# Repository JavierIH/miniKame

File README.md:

> 📌 **A newer and more advanced version of this robot is available:** [Kame32](https://github.com/javierih/kame32)

# Kame (MiniKame)

[What components do I need for building this robot?](https://github.com/bqlabs/miniKame/wiki/BOM)

[Where can I find the assembly model?](https://github.com/bqlabs/miniKame/blob/develop/parts/freecad/miniKame.fcstd)

[How are servos connected to the NodeMCU V2 board?](https://github.com/JavierIH/miniKame/wiki/Map-between-servos-and-board-pins)

# License

Son of [Kame](https://github.com/bqlabs/kame)

# Remixes
[PoorKame](https://github.com/owenlab/PoorKame) by [owenlab](https://github.com/owenlab)

[FatKame](https://github.com/Blomdoft/fatKame) by [Blomdoft](https://github.com/Blomdoft)

# Other

Sponsored by BQ till march 2016

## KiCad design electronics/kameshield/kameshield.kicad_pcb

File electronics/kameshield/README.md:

# Attention:

This PCB is just a proof of concept of a shield for putting together the needed connectors for servos and battery on a NodeMCU V2. At this time, it has been fabricated an only one board (the one is actually being mounted on PoorKame) with a hobby-level milling machine, so I can't guarantee it to work or even if it is safe for being used with another specific hardware.

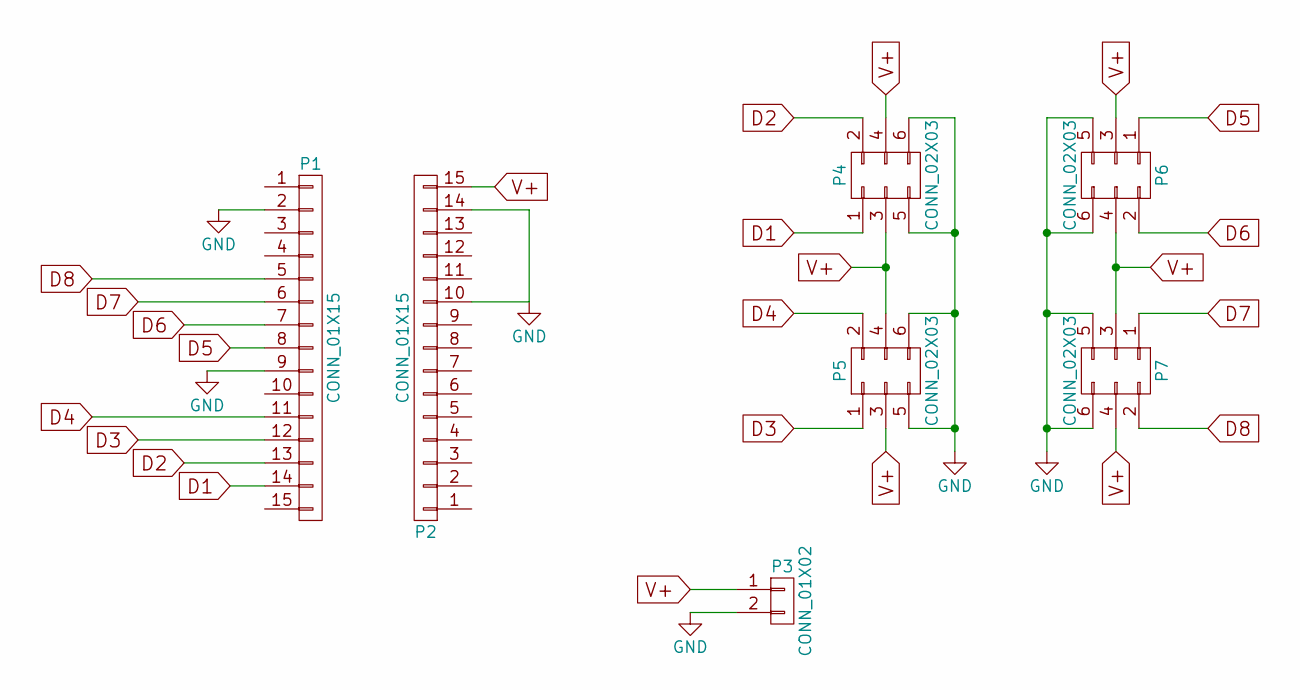
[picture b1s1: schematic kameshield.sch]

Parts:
P1, P2: CONN_01X15; Pin_Header_Straight_1x15
P3: CONN_01X02; Pin_Header_Straight_1x02
P4, P5, P6, P7: CONN_02X03; Pin_Header_Angled_2x03

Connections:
D1: P1.14, P4.1
D2: P1.13, P4.2
D3: P1.12, P5.1
D4: P1.11, P5.2
D5: P1.8, P6.1
D6: P1.7, P6.2
D7: P1.6, P7.1
D8: P1.5, P7.2
GND: P1.2, P1.9, P2.10, P2.14, P3.2, P4.5, P4.6, P5.5, P5.6, P6.5, P6.6, P7.5, P7.6
V+: P2.15, P3.1, P4.3, P4.4, P5.3, P5.4, P6.3, P6.4, P7.3, P7.4

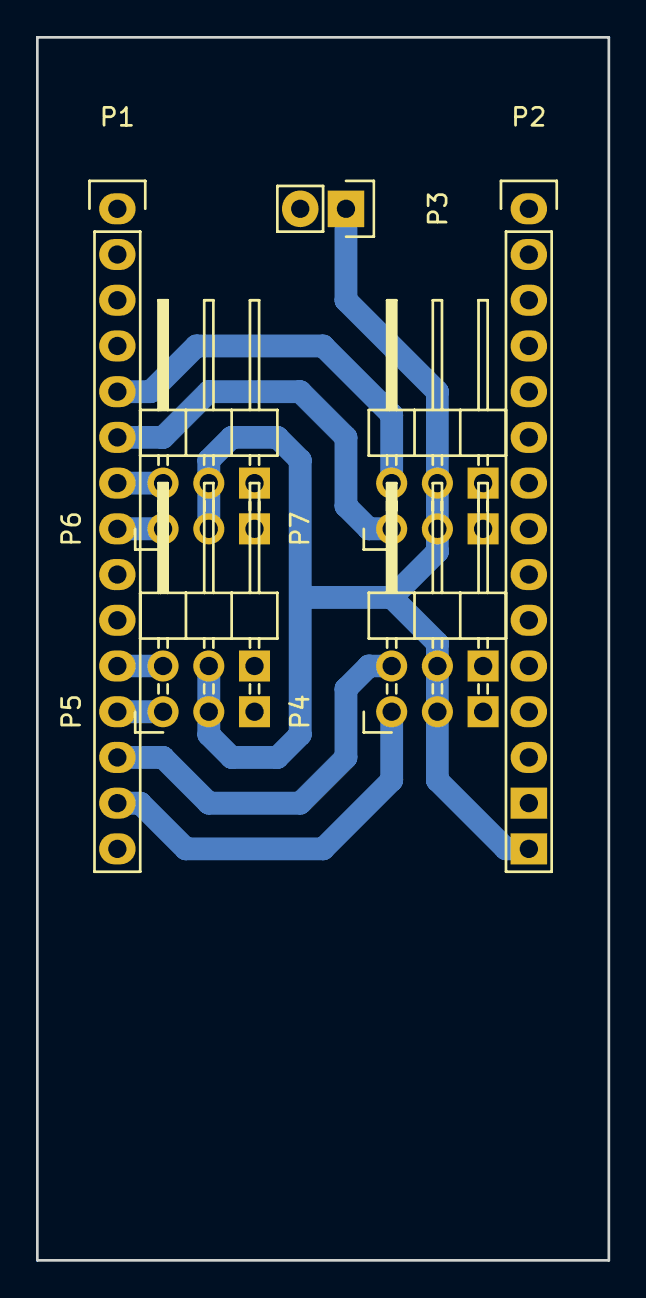
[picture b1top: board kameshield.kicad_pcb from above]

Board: 2 copper layers, 31.8 x 67.9 mm, 7 parts (0 on the bottom side), 10 nets.

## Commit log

2015-11-26 Add freecad project
2015-11-26 Add stl files
2015-11-30 updated body for nodemcu
2015-12-01 reinforced bearing cavitiy on legB
2015-12-01 Added bearings on 3d model
2015-12-02 added code structure
2015-12-02 moved ardusnake from src to lib
2015-12-14 updated 3d model
2015-12-14 new oscillator library
2015-12-15 added spacers for the body-bracket joint
2015-12-16 walk and home functions
2015-12-16 added new minikame library
2015-12-17 basic server and client
2015-12-17 implemented speed control
2015-12-22 Added new functions and solved reset bug
2016-01-11 Added bolts and nuts on freecad project
2016-01-11 Added bolts for yaw servos
2016-01-11 Generated stl files for leg parts
2016-01-11 Deleted duplicated files
2016-01-11 Images of individual parts
2016-01-11 doc images
2016-01-13 generated step parts
2016-01-25 Added an experimental shield (not working yey
2016-01-27 body support
2016-01-27 generated stl
2016-01-27 modded support
2016-03-08 shield for kame
2016-03-11 main image
2016-03-21 Added new functions
2016-03-30 last commit
2016-04-20 Update README with remixes
2016-06-14 updates octosnake and solves calibration bug
2016-06-14 add omniWalk function
2016-06-16 omniwalk calibration
2016-07-18 Fix IP print at the start
2017-01-11 regenerated gerbers and added a solder mask
2017-01-11 added readme for the shield
2017-02-17 fixed warnings, added comments
2017-02-17 scheme of connections
2017-02-27 uploading the correct body part. fix #3

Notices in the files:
README.md:
License:
doc/images/by-sa.png
